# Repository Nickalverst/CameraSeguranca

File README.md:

# CameraSeguranca
Projeto Câmera de Segurança desenvolvido ao longo da disciplina de Oficinas de Integração I do curso de Engenharia de Computação da Universidade Tecnológica Federal do Paraná.

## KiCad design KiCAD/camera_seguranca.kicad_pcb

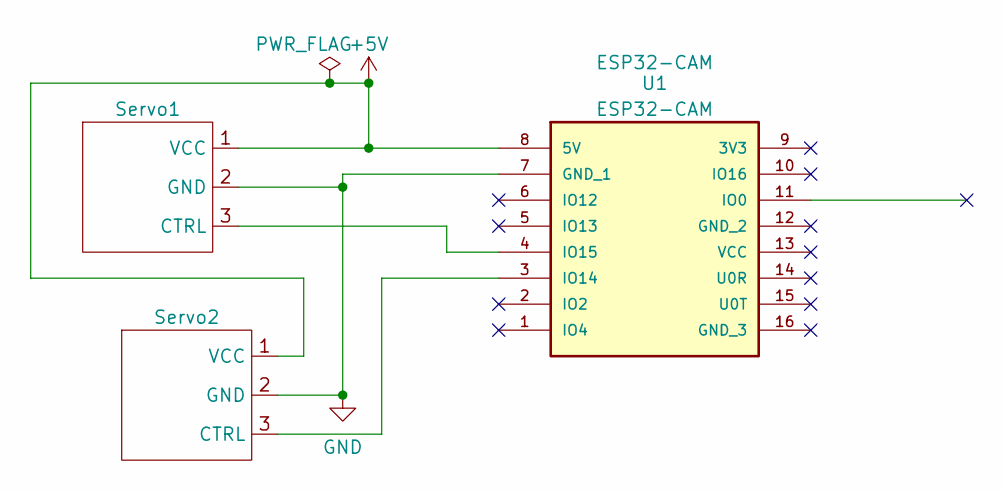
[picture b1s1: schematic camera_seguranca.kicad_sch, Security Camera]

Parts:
Servo1, Servo2: ServoG9
U1: ESP32-CAM; MANUFACTURER_PART_NUMBER ESP32-CAM

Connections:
+5V: Servo1.1 (VCC), Servo2.1 (VCC), U1.8 (5V)
GND: Servo1.2 (GND), Servo2.2 (GND), U1.7 (GND_1)
unnamed: Servo1.3 (CTRL), U1.4 (IO15)
unnamed: Servo2.3 (CTRL), U1.3 (IO14)

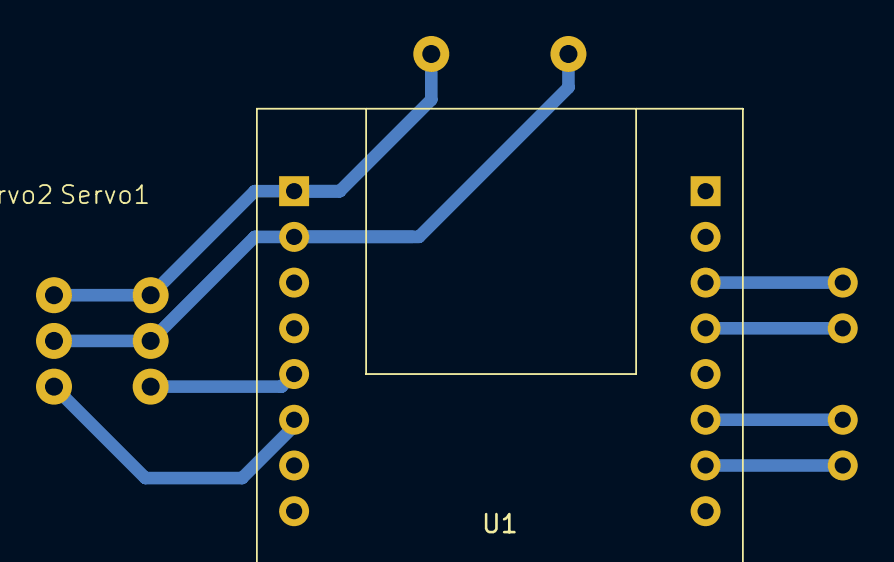
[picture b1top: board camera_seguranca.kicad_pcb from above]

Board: 2 copper layers, 3 parts (0 on the bottom side), 4 nets.
